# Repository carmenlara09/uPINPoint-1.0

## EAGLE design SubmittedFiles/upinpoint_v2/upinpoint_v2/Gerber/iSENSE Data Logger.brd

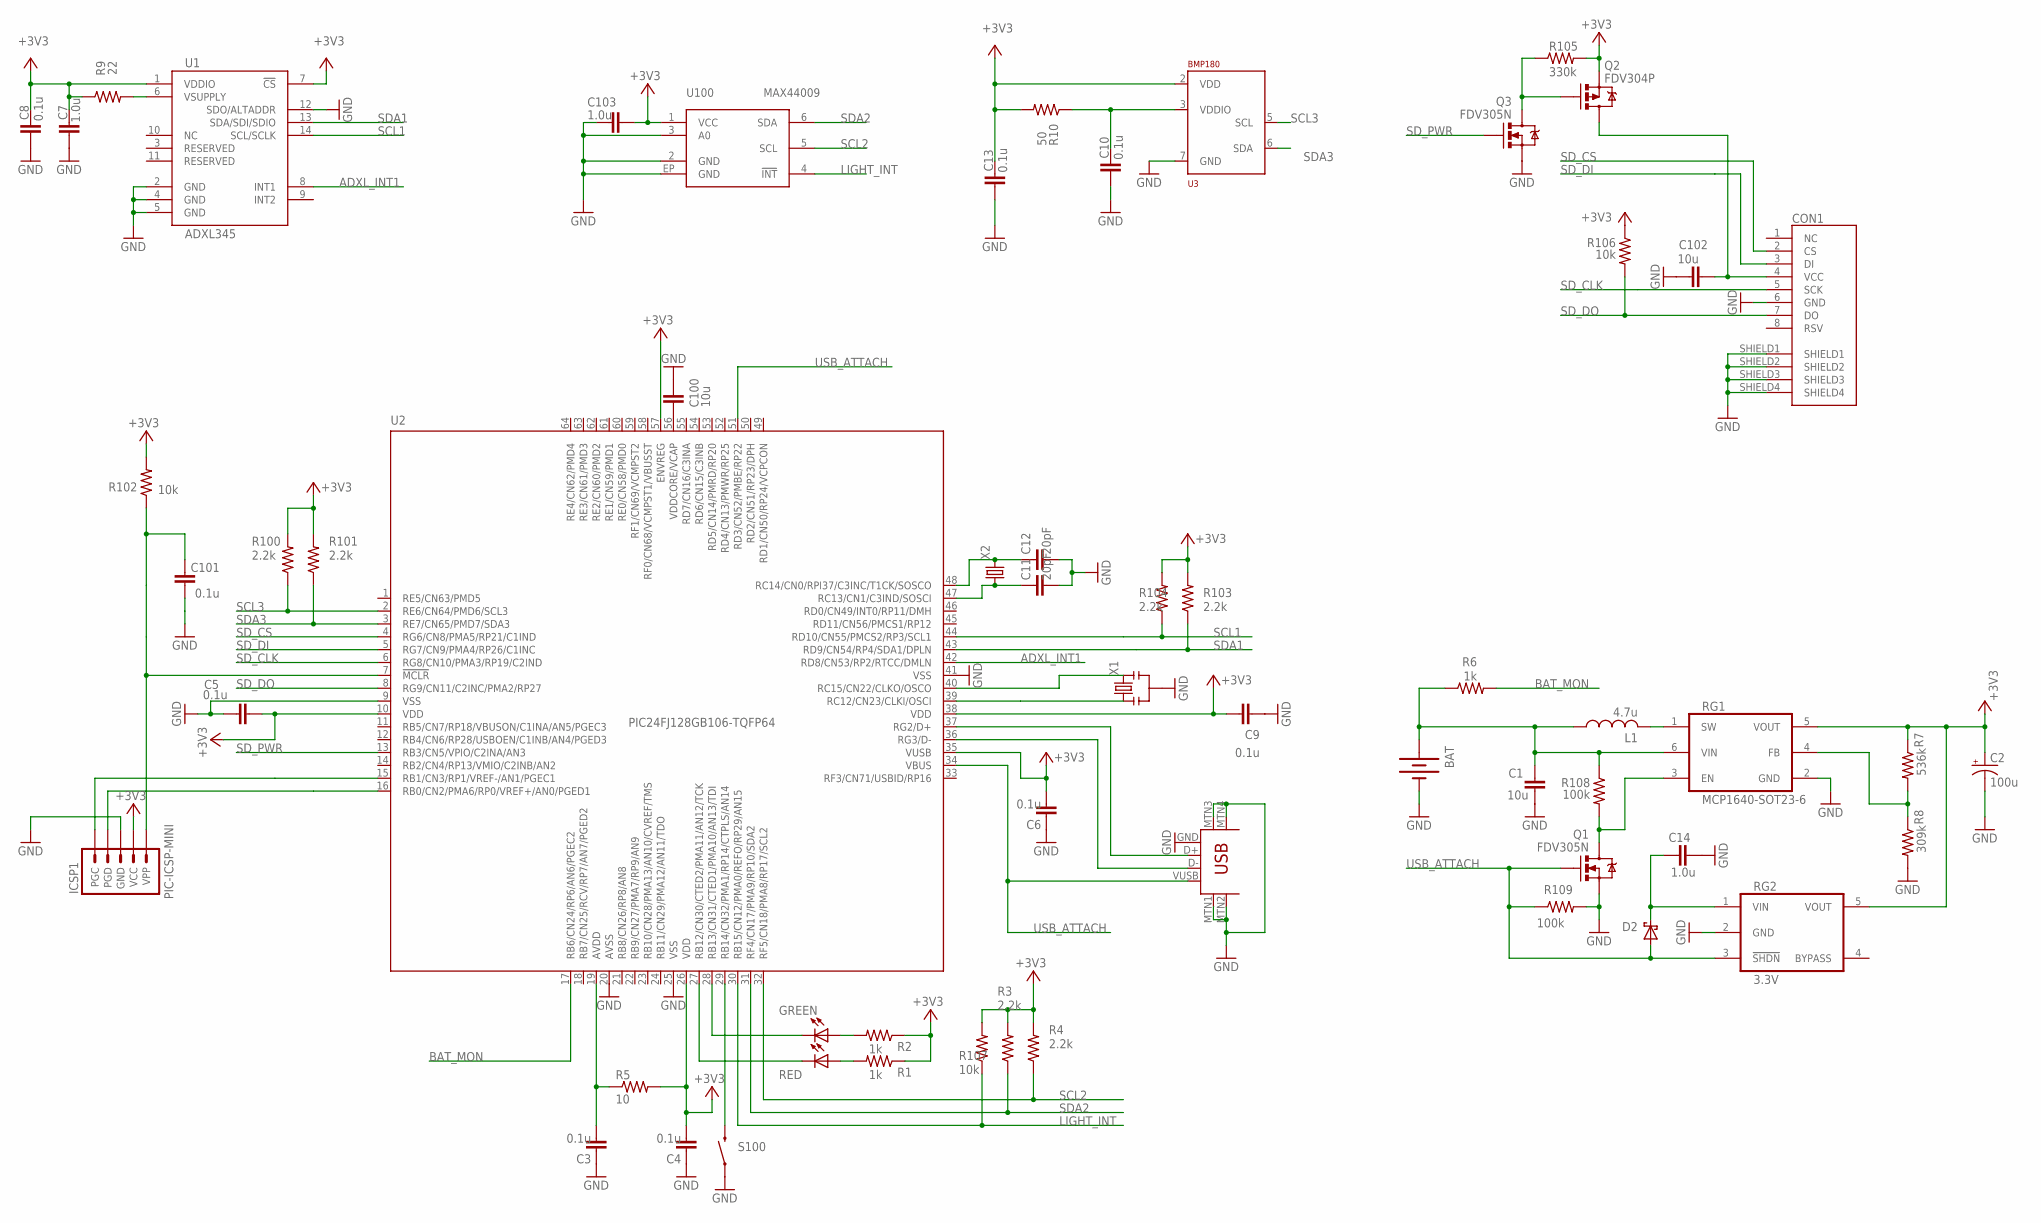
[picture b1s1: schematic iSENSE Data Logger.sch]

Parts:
BAT: BATTERY-AAA-PCB-1-NO-HOLES; BATTERY_HOLDER_AAA_KEYSTONE_2466_NO_HOLES; DIGIKEY_PN 2466K-ND
C1, C100: 10u; RCL_0603
C2: 100u; CT3528
C3, C4, C5, C6, C8, C9, C10, C13, C101: 0.1u; RCL_0402
C7, C103: 1.0u; RCL_0402
C11, C12: 20pF; RCL_0402
C14: 1.0u; RCL_0603
C102: 10u; RCL_0402
CON1: SOCKET_SD_CARD_MICRO-AMP-101-00303-68; SOCKET_SD_CARD_MICRO
D2: DIODE_SCHOTTKY-SOD523; SOD523
GREEN: GREEN; LED_0603
ICSP1: PIC-ICSP-MINI
L1: 4.7u; INDUCTOR_3MM_X_3MM
Q1, Q3: FDV305N; SOT23-3
Q2: FDV304P; SOT23-3
R1, R2, R6: 1k; RCL_0402
R3, R4, R100, R101, R103, R104: 2.2k; RCL_0402
R5: 10; RCL_0402
R7: 536k; RCL_0402
R8: 309k; RCL_0402
R9: 22; RCL_0402
R10: 50; RCL_0402
R102, R106, R107: 10k; RCL_0402
R105: 330k; RCL_0402
R108, R109: 100k; RCL_0402
RED: RED; LED_0603
RG1: MCP1640-SOT23-6; SOT23-6
RG2: 3.3V; SOT23-5
S100: SWITCH_MOMENTARY-SMD-RA; SWITCH_TACTILE_SMD_RA
U1: ADXL345; LGA14
U2: PIC24FJ128GB106-TQFP64; TQFP64-10X10
U3: BMP180; LGA7
U100: MAX44009; UTDFN-OPTO
USB100: CON_USB_4_PIN-A_MALE; CON_USB_A_MALE_CNC_TECH_1001-010-01001
X1: CERAMIC_RESONATOR_3_PIN-2MM_X_4.5MM; CERAMIC_RESONATOR_MURATA_2X4.5
X2: CRYSTAL_2_PIN-4.9MM_X_1.8MM; CRYSTAL_ABRACON_ABS10

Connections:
+3V3: C2.+, C4.2, C5.1, C6.2, C7.2, C8.2, C9.1, C13.2, C103.1, ICSP1.2 (VCC), Q2.2 (S), R1.1, R2.1, R3.2, R4.2, R5.2, R7.1, R9.1, R10.2, R100.2, R101.2, R102.2, R103.2, R104.2, R105.2, R106.1, R107.2, RG1.5 (VOUT), RG2.5 (VOUT), U1.1 (VDDIO), U1.7 (!CS!), U2.10 (VDD), U2.26 (VDD), U2.35 (VUSB), U2.38 (VDD), U2.57 (ENVREG), U3.2 (VDD), U100.1 (VCC)
ADXL_INT1: U1.8 (INT1), U2.42 (RD8/CN53/RP2/RTCC/DMLN)
BAT_MON: R6.2, U2.17 (RB6/CN24/RP6/AN6/PGEC2)
GND: BAT.-, C1.2, C2.-, C3.1, C4.1, C5.2, C6.1, C7.1, C8.1, C9.2, C10.1, C11.2, C12.2, C13.1, C14.2, C100.2, C101.2, C102.1, C103.2, CON1.6 (GND), CON1.SHIELD1, CON1.SHIELD2, CON1.SHIELD3, CON1.SHIELD4, ICSP1.3 (GND), Q1.2 (S), Q3.2 (S), R8.2, R109.2, RG1.2 (GND), RG2.2 (GND), S100.1, U1.2 (GND), U1.4 (GND), U1.5 (GND), U1.12 (SDO/ALTADDR), U2.9 (VSS), U2.20 (AVSS), U2.25 (VSS), U2.41 (VSS), U3.7 (GND), U100.2 (GND), U100.3 (A0), U100.EP (GND), USB100.GND, USB100.MTN1, USB100.MTN2, USB100.MTN3, USB100.MTN4, X1.2
LIGHT_INT: R107.1, U2.30 (RB15/CN12/PMA0/REFO/RP29/AN15), U100.4 (!INT!)
unnamed: Q1.3 (D), R108.2, RG1.3 (EN)
unnamed: R9.2, U1.6 (VSUPPLY)
unnamed: C10.2, R10.1, U3.3 (VDDIO)
unnamed: GREEN.A, R2.2
unnamed: U2.39 (RC12/CN23/CLKI/OSCI), X1.1
unnamed: R1.2, RED.A
unnamed: C14.1, D2.C, RG2.1 (VIN)
unnamed: BAT.+, C1.1, L1.1, R6.1, R108.1, RG1.6 (VIN)
unnamed: L1.2, RG1.1 (SW)
unnamed: R7.2, R8.1, RG1.4 (FB)
unnamed: GREEN.C, U2.28 (RB13/CN31/CTED1/PMA10/AN13/TDI)
unnamed: RED.C, U2.27 (RB12/CN30/CTED2/PMA11/AN12/TCK)
unnamed: C11.1, U2.47 (RC13/CN1/C3IND/SOSCI), X2.1
unnamed: C12.1, U2.48 (RC14/CN0/RPI37/C3INC/T1CK/SOSCO), X2.2
unnamed: S100.2, U2.29 (RB14/CN32/PMA1/RP14/CTPLS/AN14)
unnamed: C102.2, CON1.4 (VCC), Q2.3 (D)
unnamed: Q2.1 (G), Q3.3 (D), R105.1
unnamed: U2.40 (RC15/CN22/CLKO/OSCO), X1.3
unnamed: ICSP1.5 (PGC), U2.15 (RB1/CN3/RP1/VREF-/AN1/PGEC1)
unnamed: C100.1, U2.56 (VDDCORE/VCAP)
unnamed: C3.2, R5.1, U2.19 (AVDD)
unnamed: C101.1, ICSP1.1 (VPP), R102.1, U2.7 (!MCLR)
unnamed: ICSP1.4 (PGD), U2.16 (RB0/CN2/PMA6/RP0/VREF+/AN0/PGED1)
unnamed: U2.37 (RG2/D+), USB100.D+
unnamed: U2.36 (RG3/D-), USB100.D-
SCL1: R104.1, U1.14 (SCL/SCLK), U2.44 (RD10/CN55/PMCS2/RP3/SCL1)
SCL2: R4.1, U2.32 (RF5/CN18/PMA8/RP17/SCL2), U100.5 (SCL)
SCL3: R100.1, U2.2 (RE6/CN64/PMD6/SCL3), U3.5 (SCL)
SDA1: R103.1, U1.13 (SDA/SDI/SDIO), U2.43 (RD9/CN54/RP4/SDA1/DPLN)
SDA2: R3.1, U2.31 (RF4/CN17/PMA9/RP10/SDA2), U100.6 (SDA)
SDA3: R101.1, U2.3 (RE7/CN65/PMD7/SDA3), U3.6 (SDA)
SD_CLK: CON1.5 (SCK), U2.6 (RG8/CN10/PMA3/RP19/C2IND)
SD_CS: CON1.2 (CS), U2.4 (RG6/CN8/PMA5/RP21/C1IND)
SD_DI: CON1.3 (DI), U2.5 (RG7/CN9/PMA4/RP26/C1INC)
SD_DO: CON1.7 (DO), R106.2, U2.8 (RG9/CN11/C2INC/PMA2/RP27)
SD_PWR: Q3.1 (G), U2.13 (RB3/CN5/VPIO/C2INA/AN3)
USB_ATTACH: D2.A, Q1.1 (G), R109.1, RG2.3 (!SHDN!), U2.34 (VBUS), U2.51 (RD3/CN52/PMBE/RP22), USB100.VUSB (VBUS)

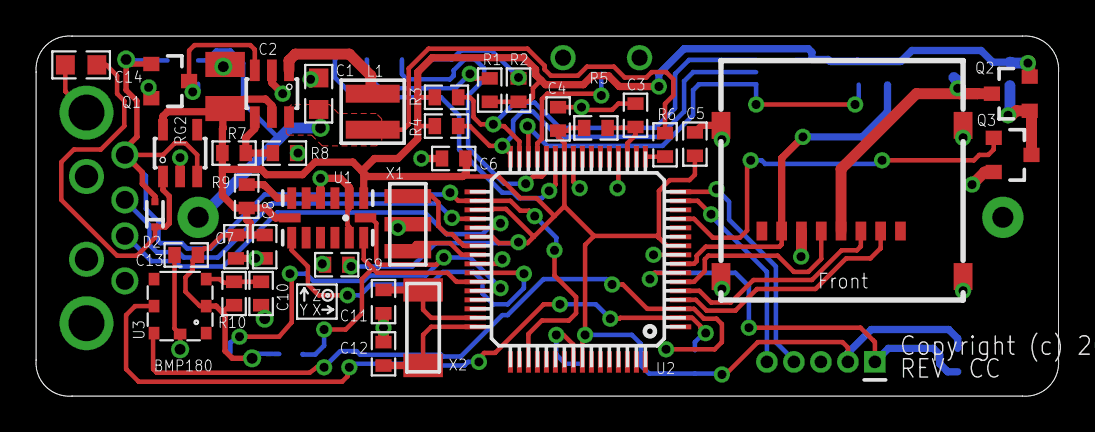
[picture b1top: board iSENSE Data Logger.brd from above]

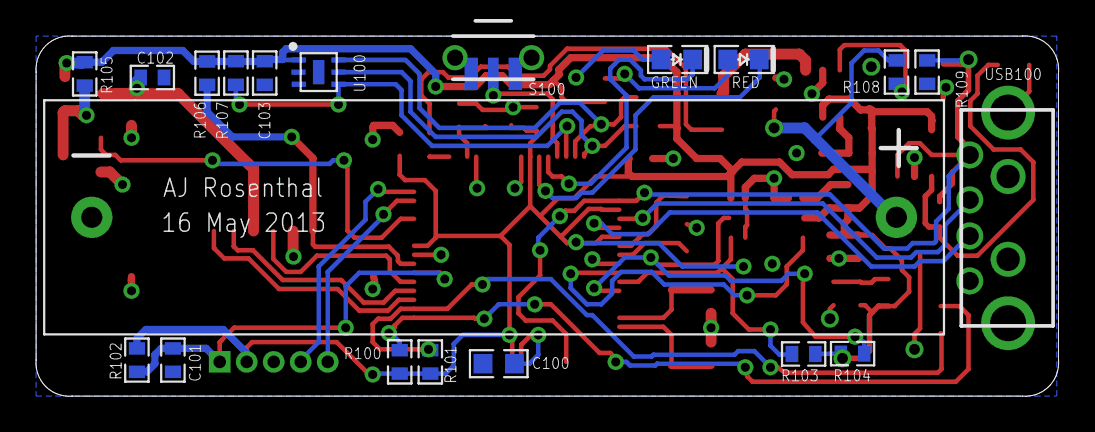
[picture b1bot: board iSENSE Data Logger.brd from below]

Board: 2 copper layers, 56.8 x 20.0 mm, 59 parts (20 on the bottom side), 42 nets.

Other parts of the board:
U$100: INFO_BOARD1

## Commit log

2013-05-31 new board layout
2013-12-03 Test to see how this thing works
2013-12-03 Adding submitted files that were sent to China
2014-01-17 Added information that tests micropinpoint software.
2014-01-17 Test file is now a .txt

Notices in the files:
SubmittedFiles/upinpoint_v2/upinpoint_v2/Gerber/iSENSE Data Logger.brd:
COPYRIGHT: Copyright (c) 2012
